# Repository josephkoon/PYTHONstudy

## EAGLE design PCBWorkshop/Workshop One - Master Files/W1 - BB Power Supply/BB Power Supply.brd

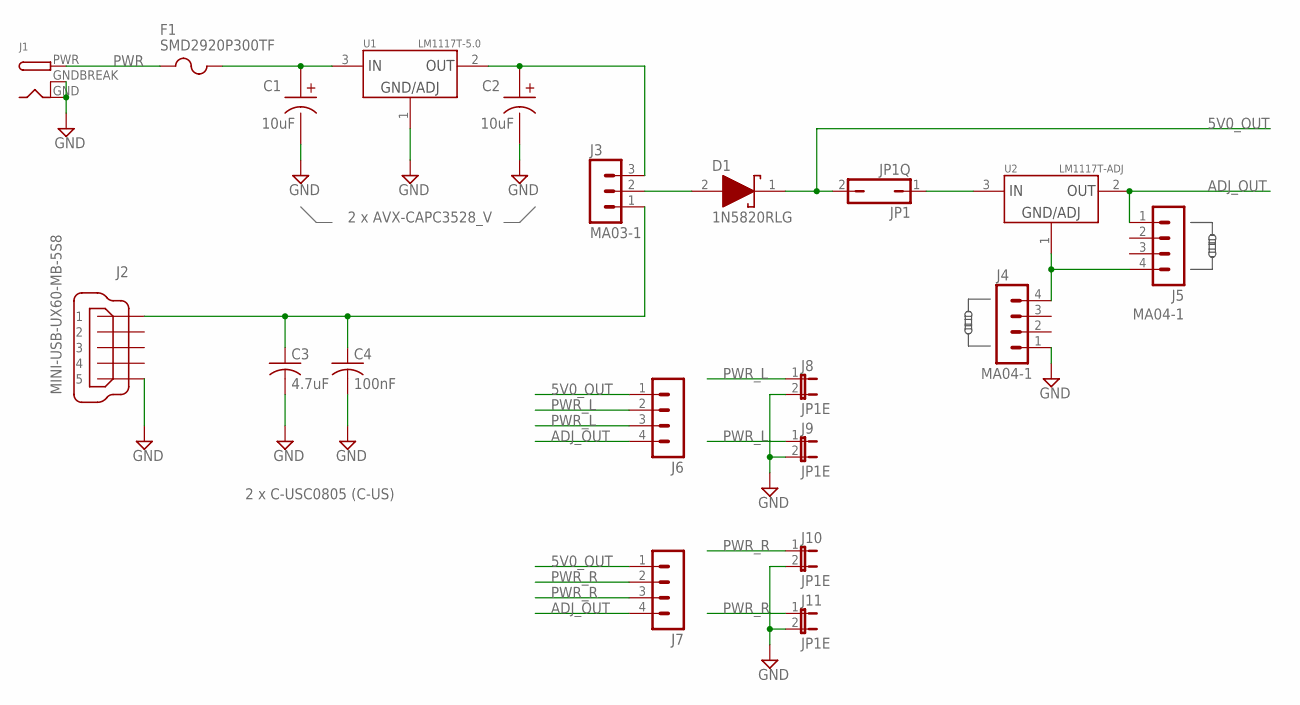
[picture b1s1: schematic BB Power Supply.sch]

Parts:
C1, C2: 10uF; AVX-CAPC3528_V
C3: 4.7uF; C0805
C4: 100nF; C0805
D1: 1N5820RLG; ONSC-AXIAL_LEAD-2-267-05_V
F1: SMD2920P300TF; FUSE2920
J1: DCBARRELPTH; DCJACK_2MM_PTH
J2: MINI-USB-UX60-MB-5S8; UX60-MB-5S8
J3: MA03-1
J4, J5, J6, J7: MA04-1
J8, J9, J10, J11: JP1E; JP1
JP1: JP1Q; JP1
U1: LM1117T-5.0; TO-220
U2: LM1117T-ADJ; TO-220

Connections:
5V0_OUT: D1.1 (K), J6.1, J7.1, JP1.2
ADJ_OUT: J5.1, J6.4, J7.4, U2.2 (OUT)
GND: C1.2, C2.2, C3.2, C4.2, J1.GND, J1.GNDBREAK, J2.5, J4.1, J8.2, J9.2, J10.2, J11.2, U1.1 (GND)
unnamed: C1.1, F1.2, U1.3 (IN)
unnamed: C2.1, J3.3, U1.2 (OUT)
unnamed: D1.2 (A), J3.2
unnamed: C3.1, C4.1, J2.1, J3.1
unnamed: JP1.1, U2.3 (IN)
unnamed: J4.4, J5.4, U2.1 (GND)
PWR: F1.1, J1.PWR
PWR_L: J6.2, J6.3, J8.1, J9.1
PWR_R: J7.2, J7.3, J10.1, J11.1

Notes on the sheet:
2 x C-USC0805 (C-US)
2 x AVX-CAPC3528_V
SMD2920P300TF

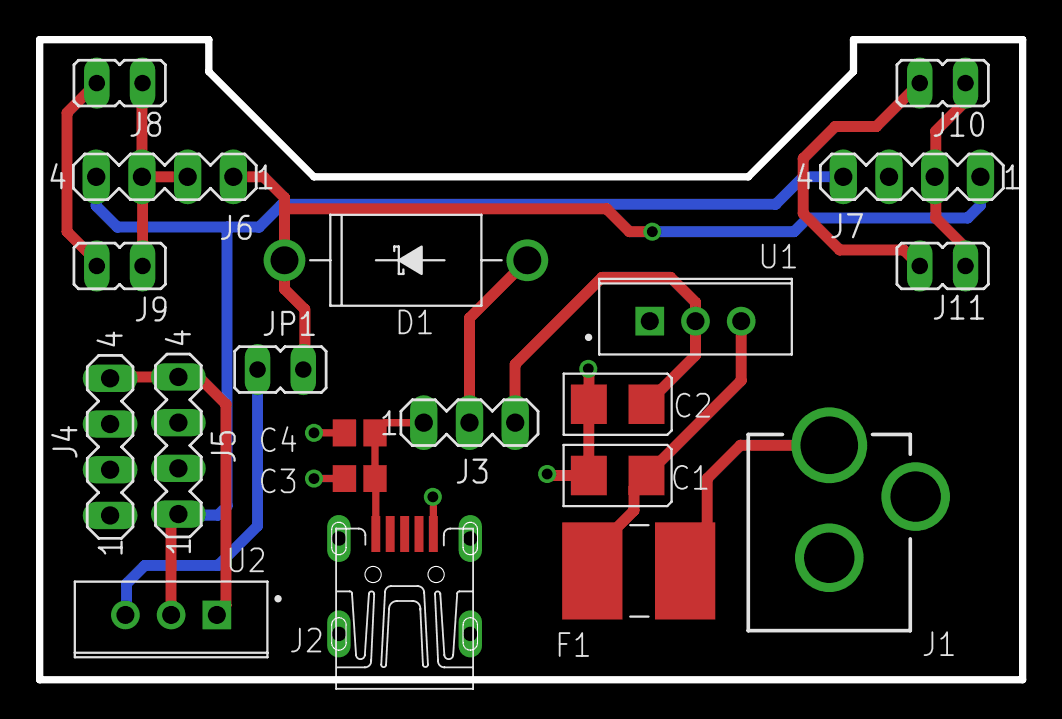
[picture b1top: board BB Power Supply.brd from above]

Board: 2 copper layers, 54.6 x 35.6 mm, 20 parts (0 on the bottom side), 12 nets.
